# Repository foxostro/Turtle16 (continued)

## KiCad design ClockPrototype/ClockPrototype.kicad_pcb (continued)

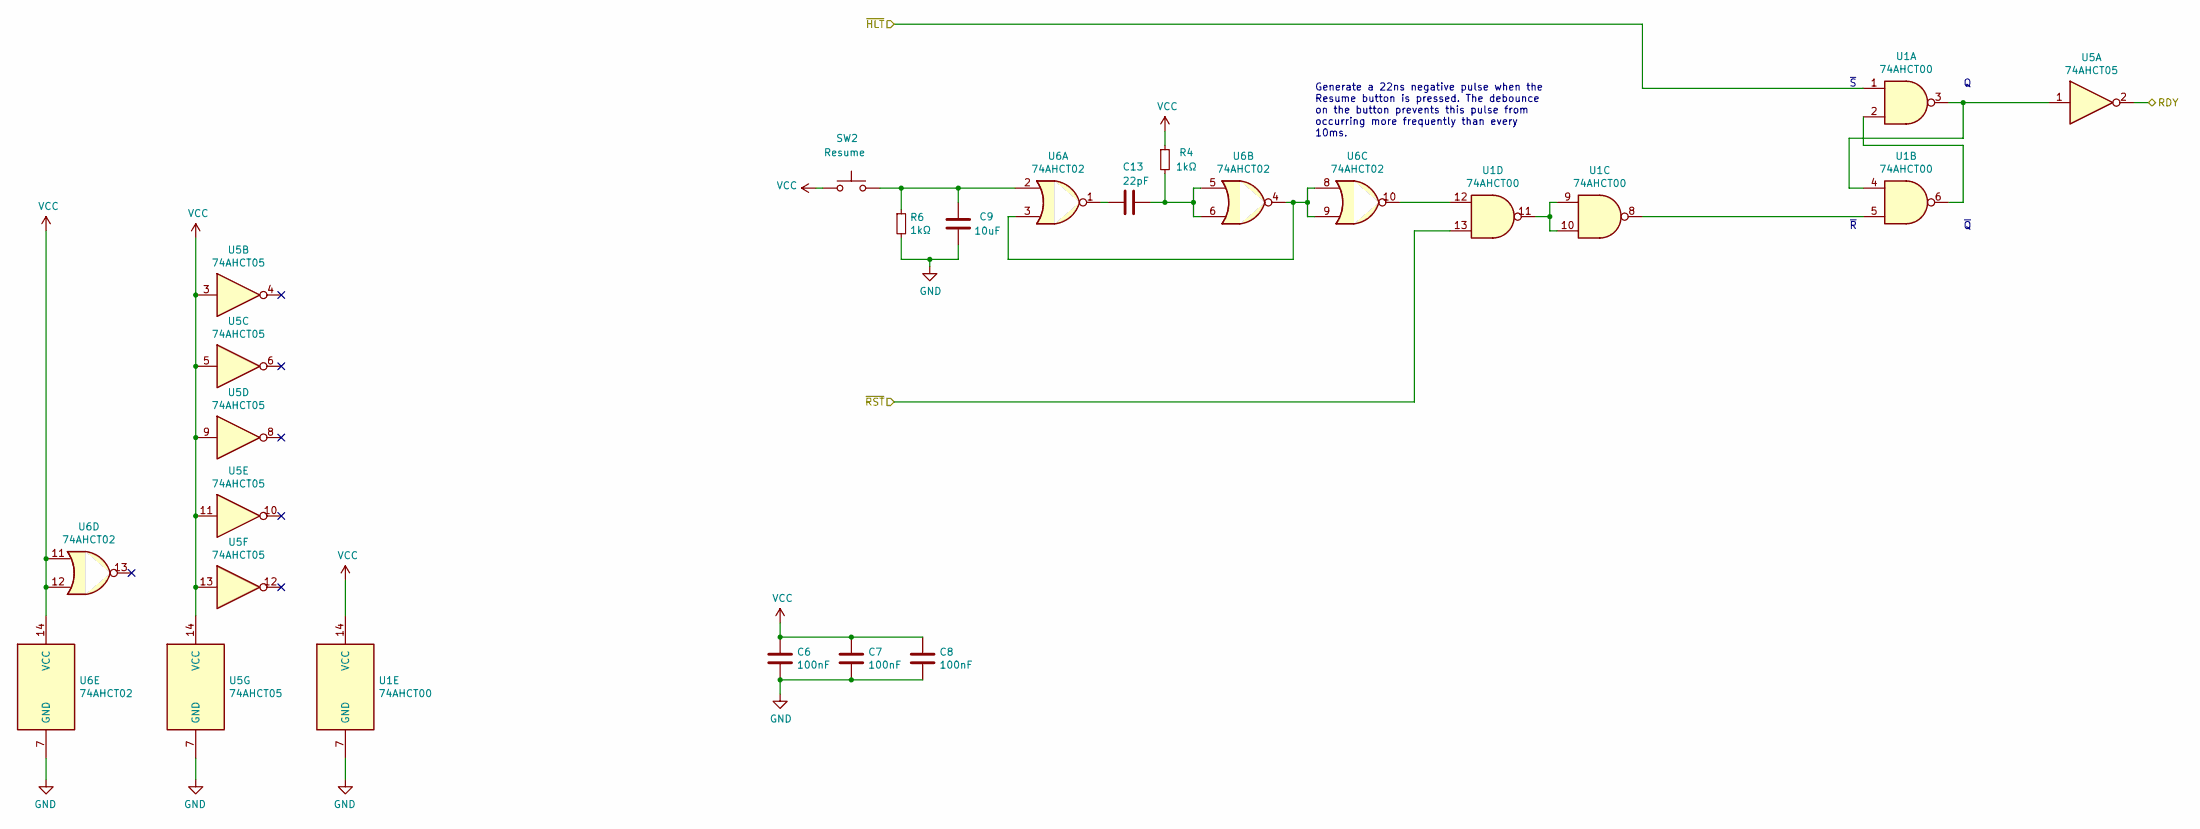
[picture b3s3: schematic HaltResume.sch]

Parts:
C6, C7, C8: 100nF; C_0603_1608Metric_Pad1.08x0.95mm_HandSolder
C9: 10uF; C_0603_1608Metric_Pad1.08x0.95mm_HandSolder
C13: 22pF; C_0603_1608Metric_Pad1.08x0.95mm_HandSolder
R4, R6: 1kΩ; R_0603_1608Metric_Pad0.98x0.95mm_HandSolder
SW2: Resume; SW_PUSH_6mm_H5mm
U1: 74AHCT00; TSSOP-14_4.4x5mm_P0.65mm
U5: 74AHCT05; TSSOP-14_4.4x5mm_P0.65mm
U6: 74AHCT02; TSSOP-14_4.4x5mm_P0.65mm

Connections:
/Clock/RDY: U5.2; also elsewhere on the board
/Clock/~HLT: U1.1; also elsewhere on the board
GND: C6.2, C7.2, C8.2, C9.2, R6.2, U1.7 (GND), U5.7 (GND), U6.7 (GND); also elsewhere on the board
unnamed: C9.1, R6.1, SW2.2, U6.2
unnamed: C13.1, R4.2, U6.5, U6.6
unnamed: C13.2, U6.1
unnamed: U1.2, U1.6
unnamed: U1.3, U1.4, U5.1
unnamed: U1.5, U1.8
unnamed: U1.9, U1.10, U1.11
unnamed: U1.12, U6.10
unnamed: U6.3, U6.4, U6.8, U6.9
VCC: C6.1, C7.1, C8.1, R4.1, SW2.1, U1.14 (VCC), U5.3, U5.5, U5.9, U5.11, U5.13, U5.14 (VCC), U6.11, U6.12, U6.14 (VCC); also elsewhere on the board
~RST: U1.13; also elsewhere on the board

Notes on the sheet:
Generate a 22ns negative pulse when the Resume button is pressed. The debounce on the button prevents this pulse from occurring more frequently than every 10ms.

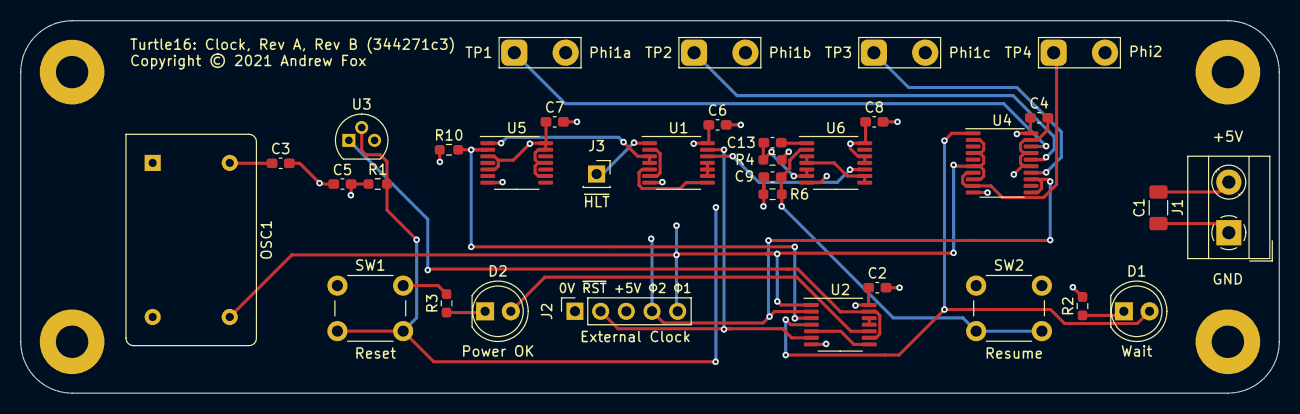
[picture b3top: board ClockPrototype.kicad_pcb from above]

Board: 4 copper layers, 124.5 x 36.8 mm, 38 parts (0 on the bottom side), 28 nets.

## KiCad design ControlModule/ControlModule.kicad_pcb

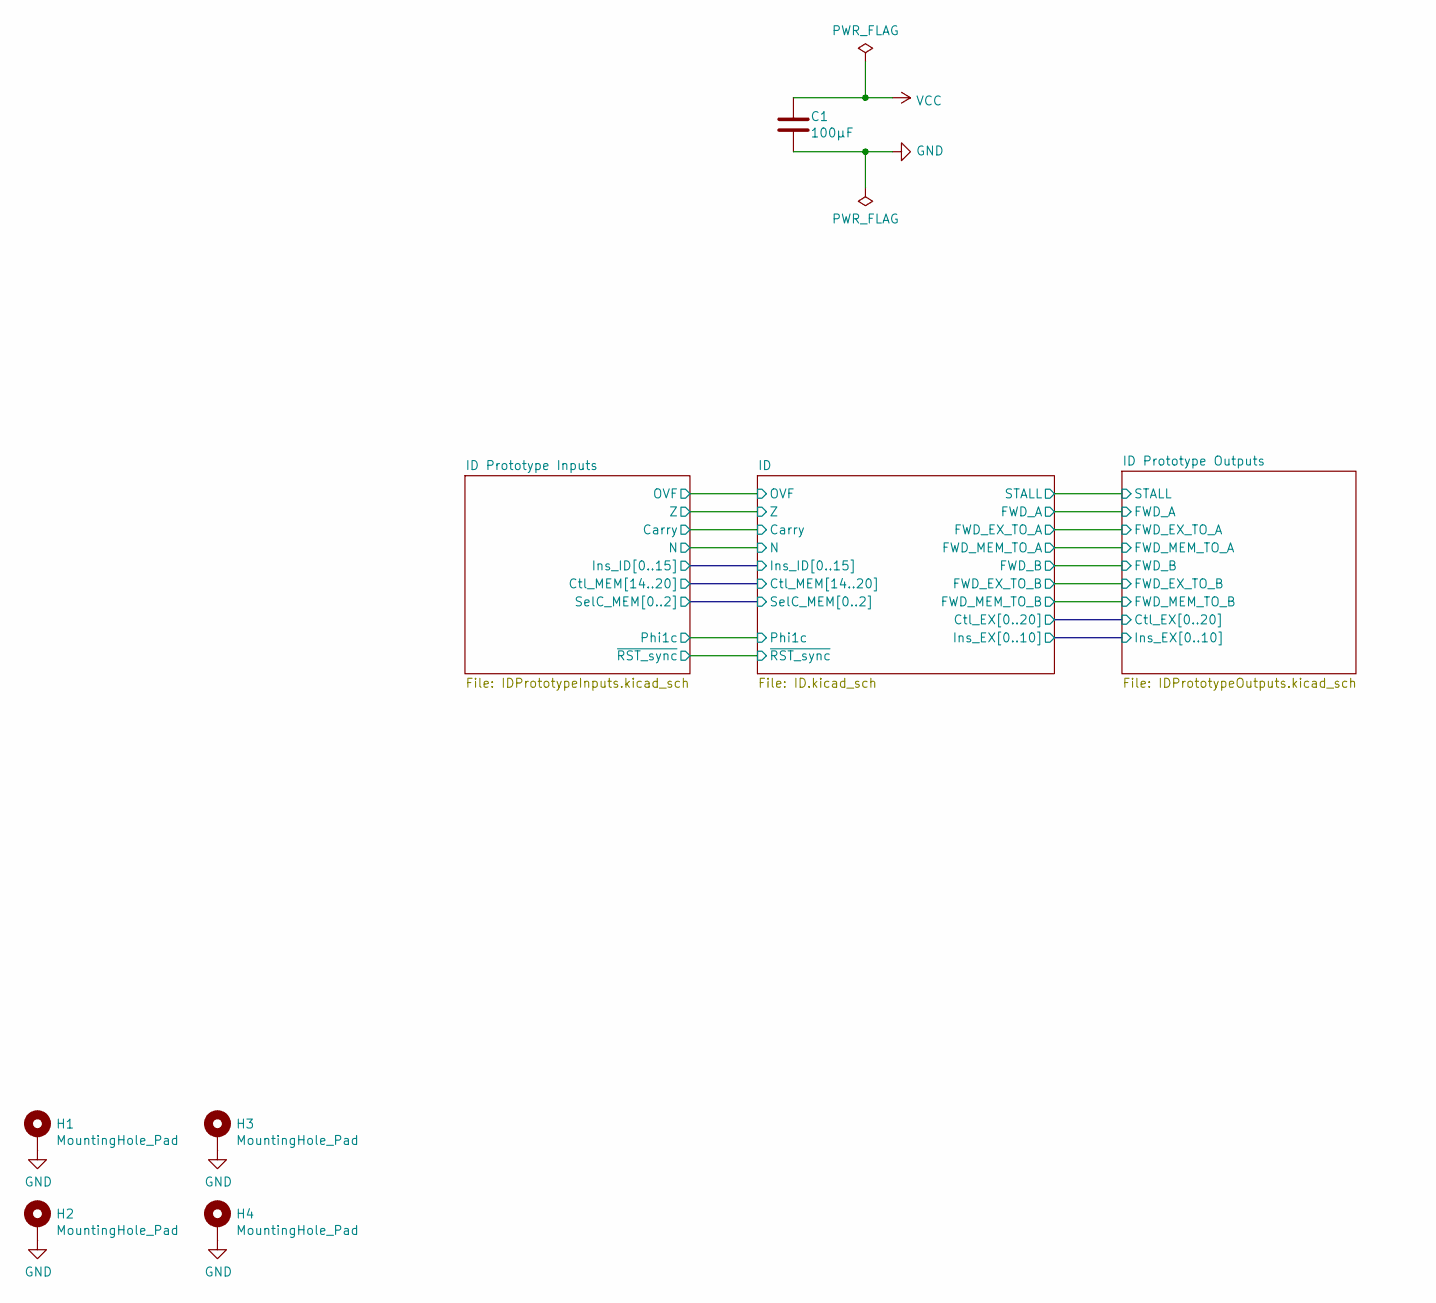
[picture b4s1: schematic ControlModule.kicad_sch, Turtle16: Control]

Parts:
C1: 100µF; C_1206_3216Metric_Pad1.33x1.80mm_HandSolder
H1, H2, H3, H4: MountingHole_Pad; MountingHole_3.2mm_M3_Pad

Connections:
GND: C1.2, H1.1, H2.1, H3.1, H4.1; also elsewhere on the board
VCC: C1.1; also elsewhere on the board

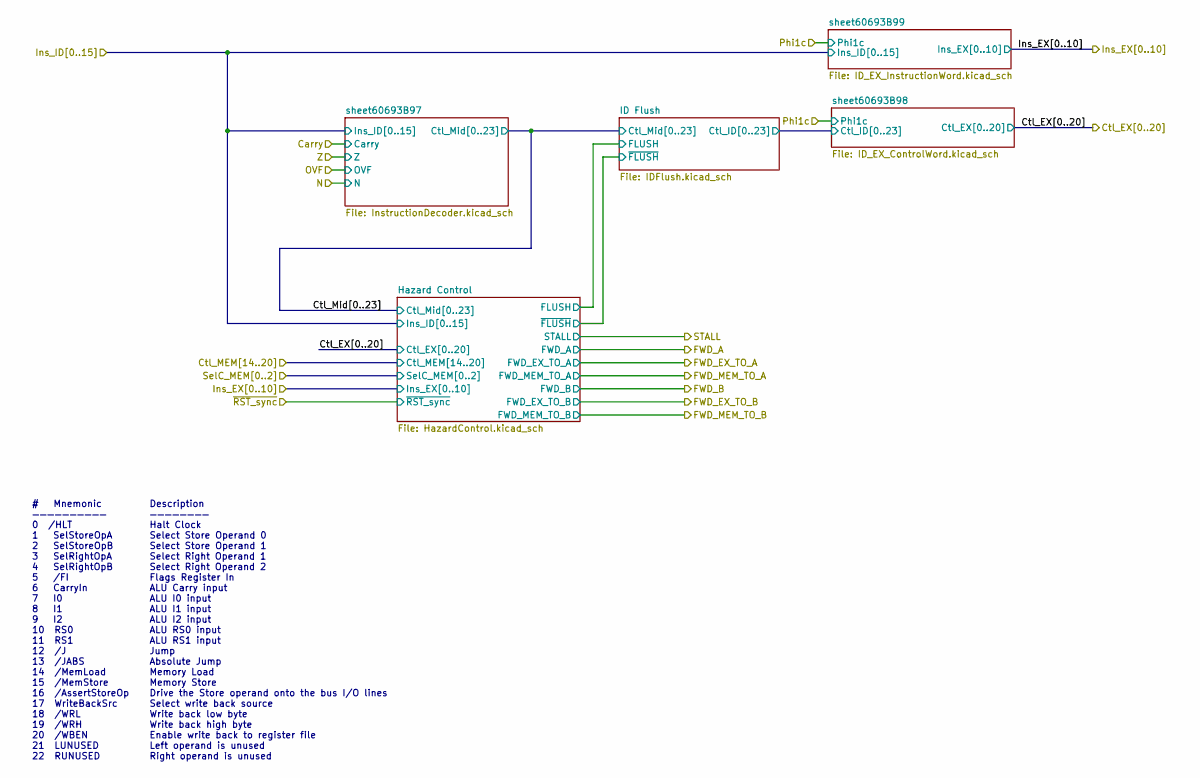
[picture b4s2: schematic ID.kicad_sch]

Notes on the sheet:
Description ———————— Halt Clock Select Store Operand 0 Select Store Operand 1 Select Right Operand 1 Select Right Operand 2 Flags Register In ALU Carry input ALU I0 input ALU I1 input ALU I2 input ALU RS0 input ALU RS1 input Jump Absolute Jump Memory Load Memory Store Drive the Store operand onto t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
# Mnemonic —————————— 0 /HLT 1 SelStoreOpA 2 SelStoreOpB 3 SelRightOpA 4 SelRightOpB 5 /FI 6 CarryIn 7 I0 8 I1 9 I2 10 RS0 11 RS1 12 /J 13 /JABS 14 /MemLoad 15 /MemStore 16 /AssertStoreOp 17 WriteBackSrc 18 /WRL 19 /WRH 20 /WBEN 21 LUNUSED 22 RUNUSED

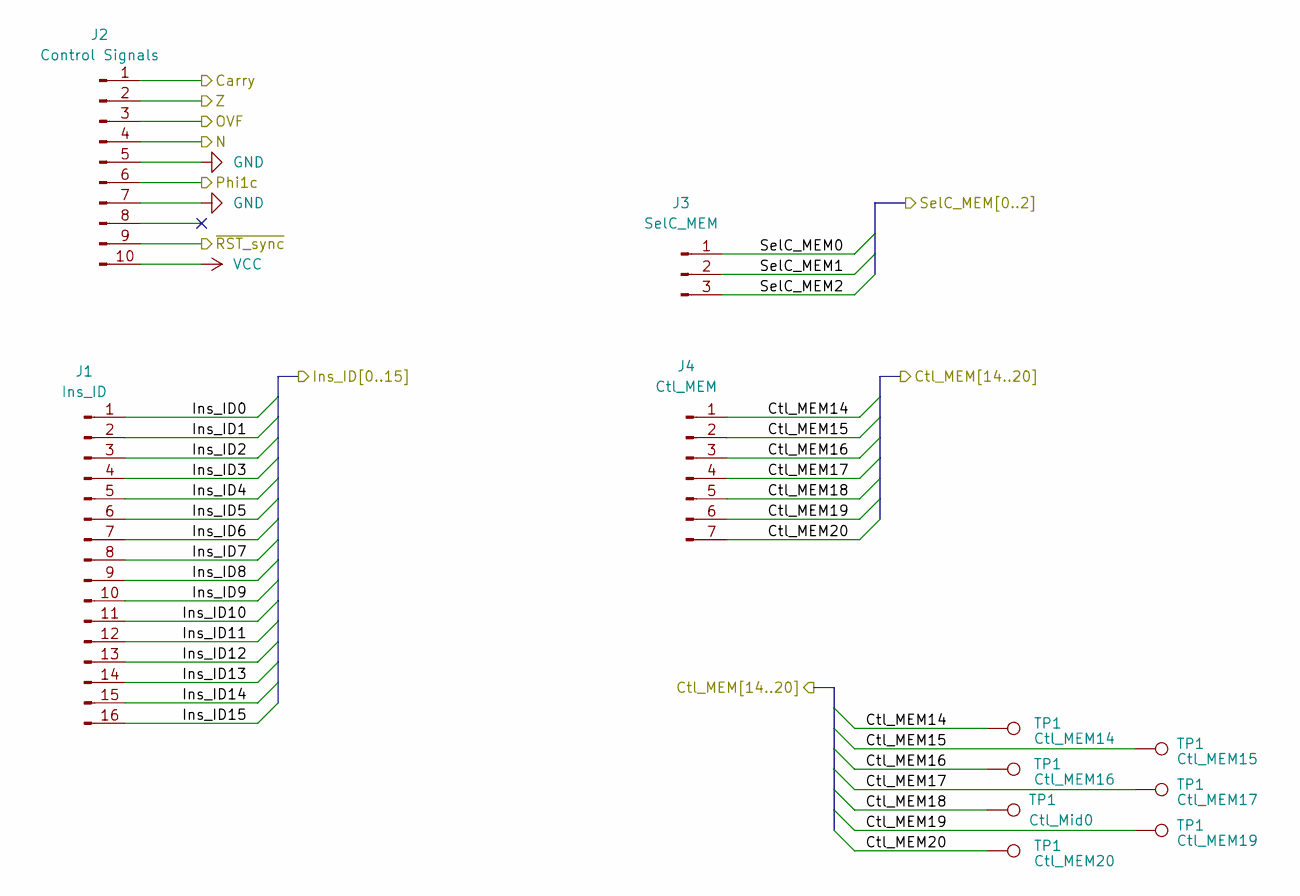
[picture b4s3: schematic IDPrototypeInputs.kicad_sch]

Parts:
J1: Ins_ID; PinHeader_1x16_P2.54mm_Vertical
J2: Control Signals; PinHeader_1x10_P2.54mm_Vertical
J3: SelC_MEM; PinHeader_1x03_P2.54mm_Vertical
J4: Ctl_MEM; PinHeader_1x07_P2.54mm_Vertical
TP1: Ctl_MEM17; TestPoint_Pad_D1.0mm

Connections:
/ID Prototype Inputs/Carry: J2.1; also elsewhere on the board
/ID Prototype Inputs/Ins_ID0: J1.1; also elsewhere on the board
/ID Prototype Inputs/Ins_ID1: J1.2; also elsewhere on the board
/ID Prototype Inputs/Ins_ID2: J1.3; also elsewhere on the board
/ID Prototype Inputs/Ins_ID3: J1.4; also elsewhere on the board
/ID Prototype Inputs/Ins_ID4: J1.5; also elsewhere on the board
/ID Prototype Inputs/Ins_ID5: J1.6; also elsewhere on the board
/ID Prototype Inputs/Ins_ID6: J1.7; also elsewhere on the board
/ID Prototype Inputs/Ins_ID7: J1.8; also elsewhere on the board
/ID Prototype Inputs/Ins_ID8: J1.9; also elsewhere on the board
/ID Prototype Inputs/Ins_ID9: J1.10; also elsewhere on the board
/ID Prototype Inputs/Ins_ID10: J1.11; also elsewhere on the board
/ID Prototype Inputs/Ins_ID11: J1.12; also elsewhere on the board
/ID Prototype Inputs/Ins_ID12: J1.13; also elsewhere on the board
/ID Prototype Inputs/Ins_ID13: J1.14; also elsewhere on the board
/ID Prototype Inputs/Ins_ID14: J1.15; also elsewhere on the board
/ID Prototype Inputs/Ins_ID15: J1.16; also elsewhere on the board
/ID Prototype Inputs/N: J2.4; also elsewhere on the board
/ID Prototype Inputs/OVF: J2.3; also elsewhere on the board
/ID Prototype Inputs/Phi1c: J2.6; also elsewhere on the board
/ID Prototype Inputs/SelC_MEM0: J3.1; also elsewhere on the board
/ID Prototype Inputs/SelC_MEM1: J3.2; also elsewhere on the board
/ID Prototype Inputs/SelC_MEM2: J3.3; also elsewhere on the board
/ID Prototype Inputs/Z: J2.2; also elsewhere on the board
/ID Prototype Inputs/~RST_sync: J2.9; also elsewhere on the board
GND: J2.5, J2.7; also elsewhere on the board
VCC: J2.10; also elsewhere on the board

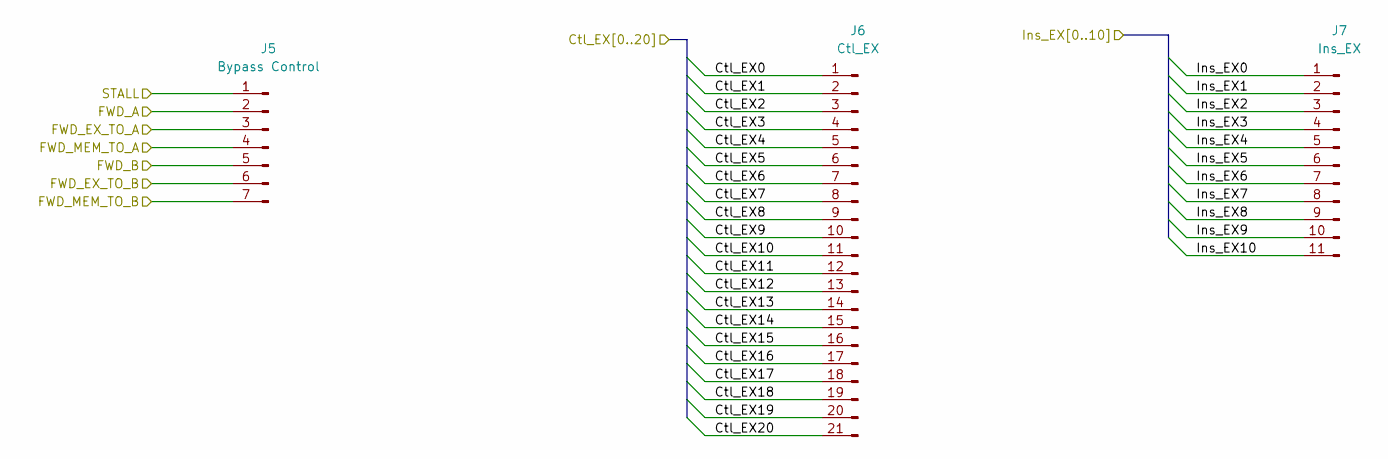
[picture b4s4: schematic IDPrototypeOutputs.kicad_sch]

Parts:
J5: Bypass Control; PinHeader_1x07_P2.54mm_Vertical
J6: Ctl_EX; PinHeader_1x21_P2.54mm_Vertical
J7: Ins_EX; PinHeader_1x11_P2.54mm_Vertical

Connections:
/ID Prototype Outputs/FWD_A: J5.2; also elsewhere on the board
/ID Prototype Outputs/FWD_B: J5.5; also elsewhere on the board
/ID Prototype Outputs/FWD_EX_TO_A: J5.3; also elsewhere on the board
/ID Prototype Outputs/FWD_EX_TO_B: J5.6; also elsewhere on the board
/ID Prototype Outputs/FWD_MEM_TO_A: J5.4; also elsewhere on the board
/ID Prototype Outputs/FWD_MEM_TO_B: J5.7; also elsewhere on the board
/ID Prototype Outputs/Ins_EX0: J7.1; also elsewhere on the board
/ID Prototype Outputs/Ins_EX1: J7.2; also elsewhere on the board
/ID Prototype Outputs/Ins_EX2: J7.3; also elsewhere on the board
/ID Prototype Outputs/Ins_EX3: J7.4; also elsewhere on the board
/ID Prototype Outputs/Ins_EX4: J7.5; also elsewhere on the board
/ID Prototype Outputs/Ins_EX5: J7.6; also elsewhere on the board
/ID Prototype Outputs/Ins_EX6: J7.7; also elsewhere on the board
/ID Prototype Outputs/Ins_EX7: J7.8; also elsewhere on the board
/ID Prototype Outputs/Ins_EX8: J7.9; also elsewhere on the board
/ID Prototype Outputs/Ins_EX9: J7.10; also elsewhere on the board
/ID Prototype Outputs/Ins_EX10: J7.11; also elsewhere on the board
/ID/Ctl_EX0: J6.1; also elsewhere on the board
/ID/Ctl_EX1: J6.2; also elsewhere on the board
/ID/Ctl_EX2: J6.3; also elsewhere on the board
/ID/Ctl_EX3: J6.4; also elsewhere on the board
/ID/Ctl_EX4: J6.5; also elsewhere on the board
/ID/Ctl_EX5: J6.6; also elsewhere on the board
/ID/Ctl_EX6: J6.7; also elsewhere on the board
/ID/Ctl_EX7: J6.8; also elsewhere on the board
/ID/Ctl_EX8: J6.9; also elsewhere on the board
/ID/Ctl_EX9: J6.10; also elsewhere on the board
/ID/Ctl_EX10: J6.11; also elsewhere on the board
/ID/Ctl_EX11: J6.12; also elsewhere on the board
/ID/Ctl_EX12: J6.13; also elsewhere on the board
/ID/Ctl_EX13: J6.14; also elsewhere on the board
/ID/Ctl_EX14: J6.15; also elsewhere on the board
/ID/Ctl_EX15: J6.16; also elsewhere on the board
/ID/Ctl_EX16: J6.17; also elsewhere on the board
/ID/Ctl_EX17: J6.18; also elsewhere on the board
/ID/Ctl_EX18: J6.19; also elsewhere on the board
/ID/Ctl_EX19: J6.20; also elsewhere on the board
/ID/Ctl_EX20: J6.21; also elsewhere on the board
/ID/Hazard Control/STALL: J5.1; also elsewhere on the board

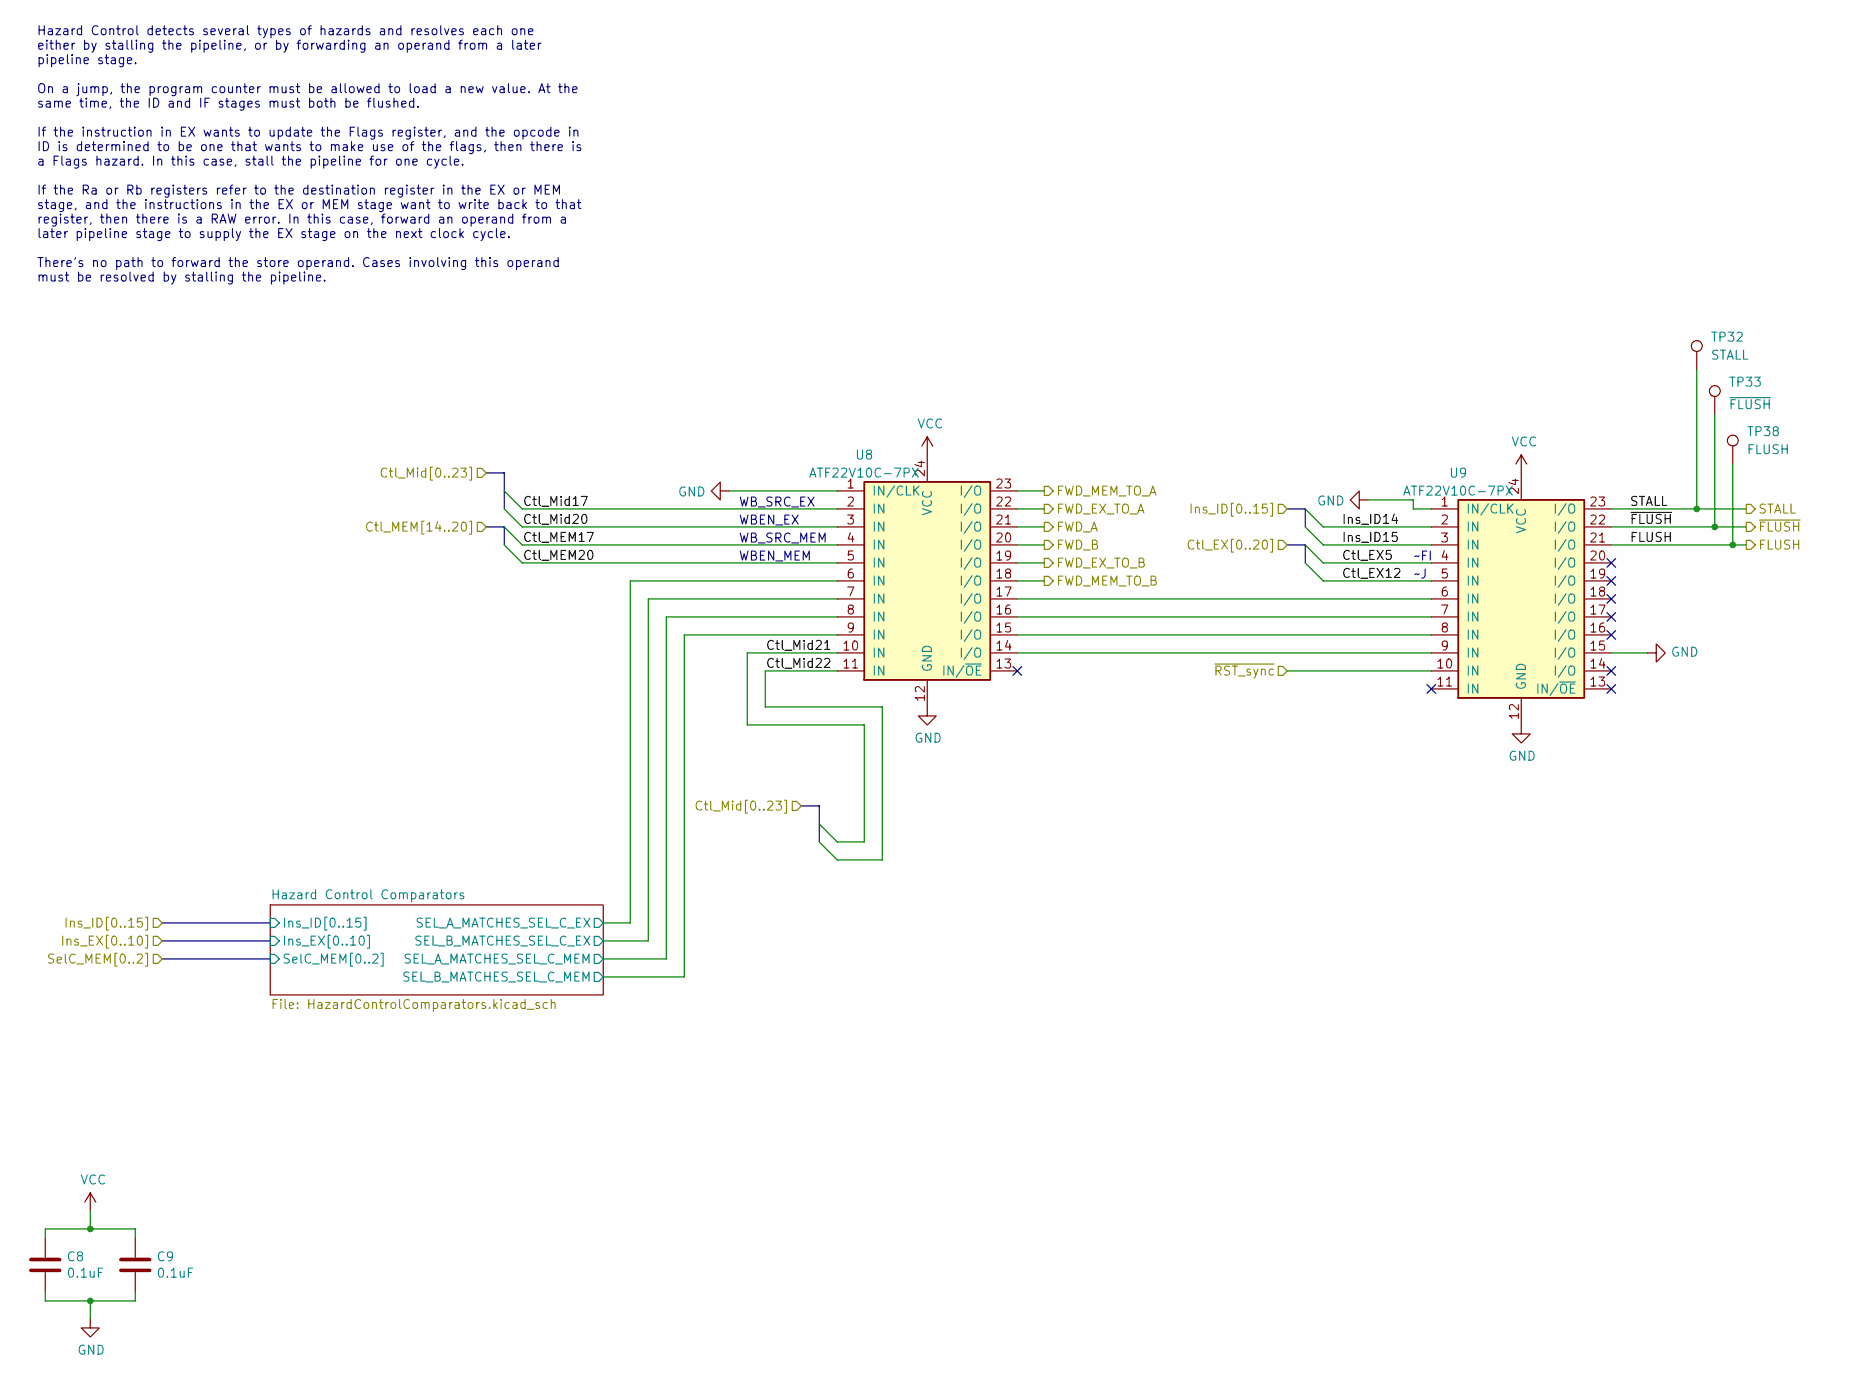
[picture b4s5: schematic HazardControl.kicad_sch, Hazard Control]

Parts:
C8, C9: 0.1uF; C_0603_1608Metric_Pad1.08x0.95mm_HandSolder
TP32: STALL; TestPoint_Pad_D1.0mm
TP33: ~{FLUSH}; TestPoint_Pad_D1.0mm
TP38: FLUSH; TestPoint_Pad_D1.0mm
U8, U9: ATF22V10C-7PX; DIP-24_W7.62mm_Socket

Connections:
/ID Prototype Inputs/Ins_ID14: U9.2 (IN); also elsewhere on the board
/ID Prototype Inputs/Ins_ID15: U9.3 (IN); also elsewhere on the board
/ID Prototype Inputs/~RST_sync: U9.10 (IN); also elsewhere on the board
/ID Prototype Outputs/FWD_A: U8.21 (I/O); also elsewhere on the board
/ID Prototype Outputs/FWD_B: U8.20 (I/O); also elsewhere on the board
/ID Prototype Outputs/FWD_EX_TO_A: U8.22 (I/O); also elsewhere on the board
/ID Prototype Outputs/FWD_EX_TO_B: U8.19 (I/O); also elsewhere on the board
/ID Prototype Outputs/FWD_MEM_TO_A: U8.23 (I/O); also elsewhere on the board
/ID Prototype Outputs/FWD_MEM_TO_B: U8.18 (I/O); also elsewhere on the board
/ID/Ctl_EX5: U9.4 (IN); also elsewhere on the board
/ID/Ctl_EX12: U9.5 (IN); also elsewhere on the board
/ID/Ctl_EX17: U8.2 (IN); also elsewhere on the board
/ID/Ctl_EX20: U8.3 (IN); also elsewhere on the board
/ID/Ctl_Mid21: U8.10 (IN); also elsewhere on the board
/ID/Ctl_Mid22: U8.11 (IN); also elsewhere on the board
/ID/Hazard Control/FLUSH: TP38.1, U9.21 (I/O); also elsewhere on the board
/ID/Hazard Control/Hazard Control Comparators/SEL_A_MATCHES_SEL_C_EX: U8.6 (IN); also elsewhere on the board
/ID/Hazard Control/Hazard Control Comparators/SEL_A_MATCHES_SEL_C_MEM: U8.8 (IN); also elsewhere on the board
/ID/Hazard Control/Hazard Control Comparators/SEL_B_MATCHES_SEL_C_EX: U8.7 (IN); also elsewhere on the board
/ID/Hazard Control/Hazard Control Comparators/SEL_B_MATCHES_SEL_C_MEM: U8.9 (IN); also elsewhere on the board
/ID/Hazard Control/STALL: TP32.1, U9.23 (I/O); also elsewhere on the board
/ID/Hazard Control/~FLUSH: TP33.1, U9.22 (I/O); also elsewhere on the board
GND: C8.2, C9.2, U8.1 (IN/CLK), U8.12 (GND), U9.1 (IN/CLK), U9.12 (GND), U9.15 (I/O); also elsewhere on the board
unnamed: U8.14 (I/O), U9.9 (IN)
unnamed: U8.15 (I/O), U9.8 (IN)
unnamed: U8.16 (I/O), U9.7 (IN)
unnamed: U8.17 (I/O), U9.6 (IN)
VCC: C8.1, C9.1, U8.24 (VCC), U9.24 (VCC); also elsewhere on the board

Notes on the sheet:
Hazard Control detects several types of hazards and resolves each one either by stalling the pipeline, or by forwarding an operand from a later pipeline stage. On a jump, the program counter must be allowed to load a new value. At the same time, the ID and IF stages must both be flushed. If the ins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
WBEN_EX
WBEN_MEM
WB_SRC_EX
~FI
WB_SRC_MEM

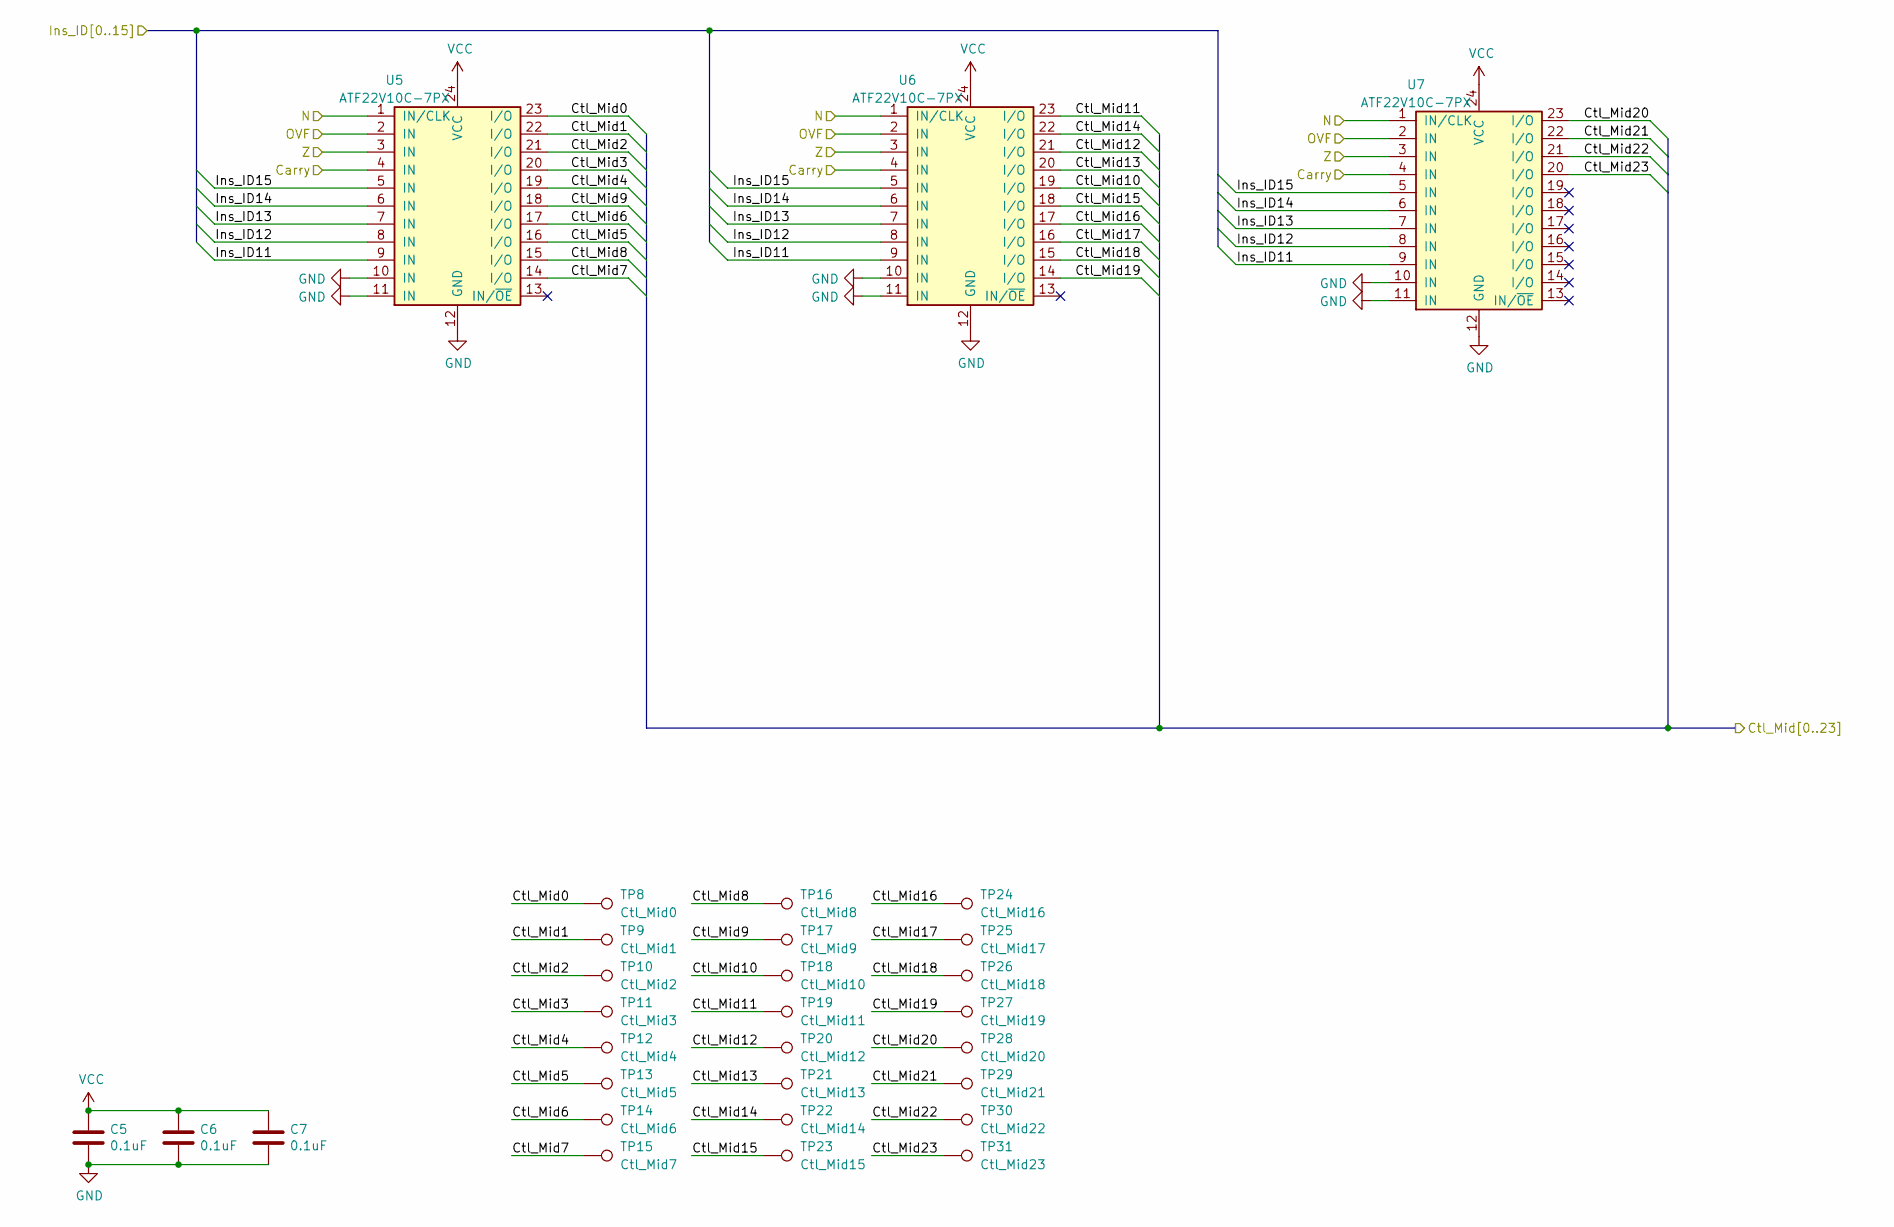
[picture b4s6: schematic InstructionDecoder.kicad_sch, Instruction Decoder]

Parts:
C5, C6, C7: 0.1uF; C_0603_1608Metric_Pad1.08x0.95mm_HandSolder
TP8: Ctl_Mid0; TestPoint_Pad_D1.0mm
TP9: Ctl_Mid1; TestPoint_Pad_D1.0mm
TP10: Ctl_Mid2; TestPoint_Pad_D1.0mm
TP11: Ctl_Mid3; TestPoint_Pad_D1.0mm
TP12: Ctl_Mid4; TestPoint_Pad_D1.0mm
TP13: Ctl_Mid5; TestPoint_Pad_D1.0mm
TP14: Ctl_Mid6; TestPoint_Pad_D1.0mm
TP15: Ctl_Mid7; TestPoint_Pad_D1.0mm
TP16: Ctl_Mid8; TestPoint_Pad_D1.0mm
TP17: Ctl_Mid9; TestPoint_Pad_D1.0mm
TP18: Ctl_Mid10; TestPoint_Pad_D1.0mm
TP19: Ctl_Mid11; TestPoint_Pad_D1.0mm
TP20: Ctl_Mid12; TestPoint_Pad_D1.0mm
TP21: Ctl_Mid13; TestPoint_Pad_D1.0mm
TP22: Ctl_Mid14; TestPoint_Pad_D1.0mm
TP23: Ctl_Mid15; TestPoint_Pad_D1.0mm
TP24: Ctl_Mid16; TestPoint_Pad_D1.0mm
TP25: Ctl_Mid17; TestPoint_Pad_D1.0mm
TP26: Ctl_Mid18; TestPoint_Pad_D1.0mm
TP27: Ctl_Mid19; TestPoint_Pad_D1.0mm
TP28: Ctl_Mid20; TestPoint_Pad_D1.0mm
TP29: Ctl_Mid21; TestPoint_Pad_D1.0mm
TP30: Ctl_Mid22; TestPoint_Pad_D1.0mm
TP31: Ctl_Mid23; TestPoint_Pad_D1.0mm
U5, U6, U7: ATF22V10C-7PX; DIP-24_W7.62mm_Socket

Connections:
/ID Prototype Inputs/Carry: U5.4 (IN), U6.4 (IN), U7.4 (IN); also elsewhere on the board
/ID Prototype Inputs/Ins_ID11: U5.9 (IN), U6.9 (IN), U7.9 (IN); also elsewhere on the board
/ID Prototype Inputs/Ins_ID12: U5.8 (IN), U6.8 (IN), U7.8 (IN); also elsewhere on the board
/ID Prototype Inputs/Ins_ID13: U5.7 (IN), U6.7 (IN), U7.7 (IN); also elsewhere on the board
/ID Prototype Inputs/Ins_ID14: U5.6 (IN), U6.6 (IN), U7.6 (IN); also elsewhere on the board
/ID Prototype Inputs/Ins_ID15: U5.5 (IN), U6.5 (IN), U7.5 (IN); also elsewhere on the board
/ID Prototype Inputs/N: U5.1 (IN/CLK), U6.1 (IN/CLK), U7.1 (IN/CLK); also elsewhere on the board
/ID Prototype Inputs/OVF: U5.2 (IN), U6.2 (IN), U7.2 (IN); also elsewhere on the board
/ID Prototype Inputs/Z: U5.3 (IN), U6.3 (IN), U7.3 (IN); also elsewhere on the board
/ID/Ctl_Mid0: TP8.1, U5.23 (I/O); also elsewhere on the board
/ID/Ctl_Mid1: TP9.1, U5.22 (I/O); also elsewhere on the board
/ID/Ctl_Mid2: TP10.1, U5.21 (I/O); also elsewhere on the board
/ID/Ctl_Mid3: TP11.1, U5.20 (I/O); also elsewhere on the board
/ID/Ctl_Mid4: TP12.1, U5.19 (I/O); also elsewhere on the board
/ID/Ctl_Mid5: TP13.1, U5.16 (I/O); also elsewhere on the board
/ID/Ctl_Mid6: TP14.1, U5.17 (I/O); also elsewhere on the board
/ID/Ctl_Mid7: TP15.1, U5.14 (I/O); also elsewhere on the board
/ID/Ctl_Mid8: TP16.1, U5.15 (I/O); also elsewhere on the board
/ID/Ctl_Mid9: TP17.1, U5.18 (I/O); also elsewhere on the board
/ID/Ctl_Mid10: TP18.1, U6.19 (I/O); also elsewhere on the board
/ID/Ctl_Mid11: TP19.1, U6.23 (I/O); also elsewhere on the board
/ID/Ctl_Mid12: TP20.1, U6.21 (I/O); also elsewhere on the board
/ID/Ctl_Mid13: TP21.1, U6.20 (I/O); also elsewhere on the board
/ID/Ctl_Mid14: TP22.1, U6.22 (I/O); also elsewhere on the board
/ID/Ctl_Mid15: TP23.1, U6.18 (I/O); also elsewhere on the board
/ID/Ctl_Mid16: TP24.1, U6.17 (I/O); also elsewhere on the board
/ID/Ctl_Mid17: TP25.1, U6.16 (I/O); also elsewhere on the board
/ID/Ctl_Mid18: TP26.1, U6.15 (I/O); also elsewhere on the board
/ID/Ctl_Mid19: TP27.1, U6.14 (I/O); also elsewhere on the board
/ID/Ctl_Mid20: TP28.1, U7.23 (I/O); also elsewhere on the board
/ID/Ctl_Mid21: TP29.1, U7.22 (I/O); also elsewhere on the board
/ID/Ctl_Mid22: TP30.1, U7.21 (I/O); also elsewhere on the board
/ID/Ctl_Mid23: TP31.1, U7.20 (I/O); also elsewhere on the board
GND: C5.2, C6.2, C7.2, U5.10 (IN), U5.11 (IN), U5.12 (GND), U6.10 (IN), U6.11 (IN), U6.12 (GND), U7.10 (IN), U7.11 (IN), U7.12 (GND); also elsewhere on the board
VCC: C5.1, C6.1, C7.1, U5.24 (VCC), U6.24 (VCC), U7.24 (VCC); also elsewhere on the board

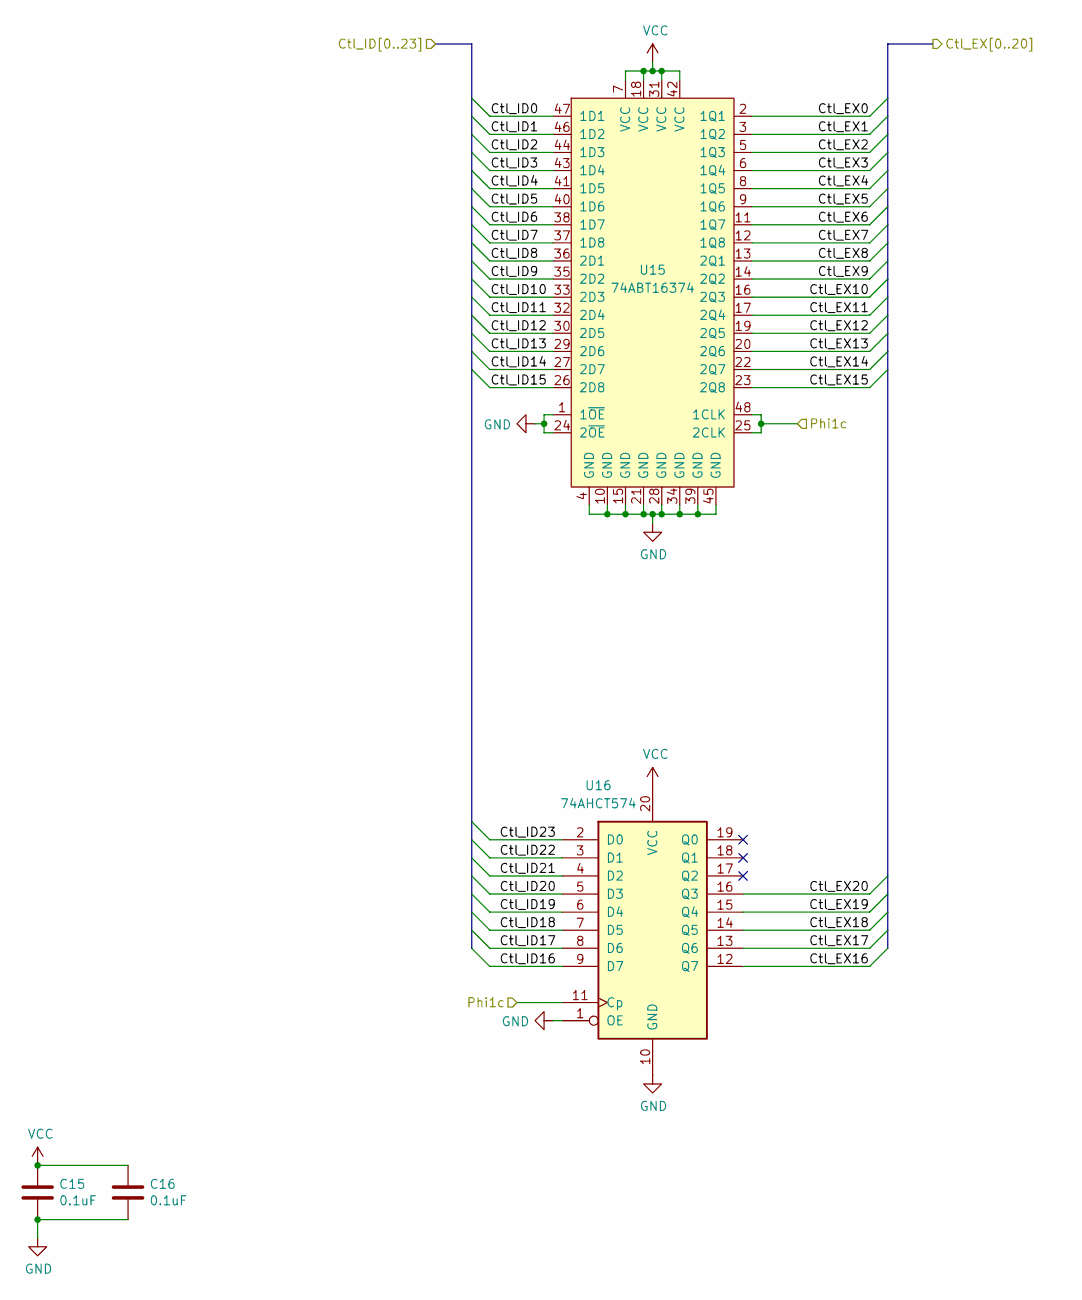
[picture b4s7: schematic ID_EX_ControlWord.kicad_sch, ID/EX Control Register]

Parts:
C15, C16: 0.1uF; C_0603_1608Metric_Pad1.08x0.95mm_HandSolder
U15: 74ABT16374; TSSOP-48_6.1x12.5mm_P0.5mm
U16: 74AHCT574; TSSOP-20_4.4x6.5mm_P0.65mm

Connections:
/ID Prototype Inputs/Phi1c: U15.25 (2CLK), U15.48 (1CLK), U16.11 (Cp); also elsewhere on the board
/ID/Ctl_EX0: U15.2 (1Q1); also elsewhere on the board
/ID/Ctl_EX1: U15.3 (1Q2); also elsewhere on the board
/ID/Ctl_EX2: U15.5 (1Q3); also elsewhere on the board
/ID/Ctl_EX3: U15.6 (1Q4); also elsewhere on the board
/ID/Ctl_EX4: U15.8 (1Q5); also elsewhere on the board
/ID/Ctl_EX5: U15.9 (1Q6); also elsewhere on the board
/ID/Ctl_EX6: U15.11 (1Q7); also elsewhere on the board
/ID/Ctl_EX7: U15.12 (1Q8); also elsewhere on the board
/ID/Ctl_EX8: U15.13 (2Q1); also elsewhere on the board
/ID/Ctl_EX9: U15.14 (2Q2); also elsewhere on the board
/ID/Ctl_EX10: U15.16 (2Q3); also elsewhere on the board
/ID/Ctl_EX11: U15.17 (2Q4); also elsewhere on the board
/ID/Ctl_EX12: U15.19 (2Q5); also elsewhere on the board
/ID/Ctl_EX13: U15.20 (2Q6); also elsewhere on the board
/ID/Ctl_EX14: U15.22 (2Q7); also elsewhere on the board
/ID/Ctl_EX15: U15.23 (2Q8); also elsewhere on the board
/ID/Ctl_EX16: U16.12 (Q7); also elsewhere on the board
/ID/Ctl_EX17: U16.13 (Q6); also elsewhere on the board
/ID/Ctl_EX18: U16.14 (Q5); also elsewhere on the board
/ID/Ctl_EX19: U16.15 (Q4); also elsewhere on the board
/ID/Ctl_EX20: U16.16 (Q3); also elsewhere on the board
/ID/ID Flush/Ctl_ID0: U15.47 (1D1); also elsewhere on the board
/ID/ID Flush/Ctl_ID1: U15.46 (1D2); also elsewhere on the board
/ID/ID Flush/Ctl_ID2: U15.44 (1D3); also elsewhere on the board
/ID/ID Flush/Ctl_ID3: U15.43 (1D4); also elsewhere on the board
/ID/ID Flush/Ctl_ID4: U15.41 (1D5); also elsewhere on the board
/ID/ID Flush/Ctl_ID5: U15.40 (1D6); also elsewhere on the board
/ID/ID Flush/Ctl_ID6: U15.38 (1D7); also elsewhere on the board
/ID/ID Flush/Ctl_ID7: U15.37 (1D8); also elsewhere on the board
/ID/ID Flush/Ctl_ID8: U15.36 (2D1); also elsewhere on the board
/ID/ID Flush/Ctl_ID9: U15.35 (2D2); also elsewhere on the board
/ID/ID Flush/Ctl_ID10: U15.33 (2D3); also elsewhere on the board
/ID/ID Flush/Ctl_ID11: U15.32 (2D4); also elsewhere on the board
/ID/ID Flush/Ctl_ID12: U15.30 (2D5); also elsewhere on the board
/ID/ID Flush/Ctl_ID13: U15.29 (2D6); also elsewhere on the board
/ID/ID Flush/Ctl_ID14: U15.27 (2D7); also elsewhere on the board
/ID/ID Flush/Ctl_ID15: U15.26 (2D8); also elsewhere on the board
/ID/ID Flush/Ctl_ID16: U16.9 (D7); also elsewhere on the board
/ID/ID Flush/Ctl_ID17: U16.8 (D6); also elsewhere on the board
/ID/ID Flush/Ctl_ID18: U16.7 (D5); also elsewhere on the board
/ID/ID Flush/Ctl_ID19: U16.6 (D4); also elsewhere on the board
/ID/ID Flush/Ctl_ID20: U16.5 (D3); also elsewhere on the board
/ID/ID Flush/Ctl_ID21: U16.4 (D2); also elsewhere on the board
/ID/ID Flush/Ctl_ID22: U16.3 (D1); also elsewhere on the board
/ID/ID Flush/Ctl_ID23: U16.2 (D0); also elsewhere on the board
GND: C15.2, C16.2, U15.1 (1~OE), U15.4 (GND), U15.10 (GND), U15.15 (GND), U15.21 (GND), U15.24 (2~OE), U15.28 (GND), U15.34 (GND), U15.39 (GND), U15.45 (GND), U16.1 (OE), U16.10 (GND); also elsewhere on the board
VCC: C15.1, C16.1, U15.7 (VCC), U15.18 (VCC), U15.31 (VCC), U15.42 (VCC), U16.20 (VCC); also elsewhere on the board
